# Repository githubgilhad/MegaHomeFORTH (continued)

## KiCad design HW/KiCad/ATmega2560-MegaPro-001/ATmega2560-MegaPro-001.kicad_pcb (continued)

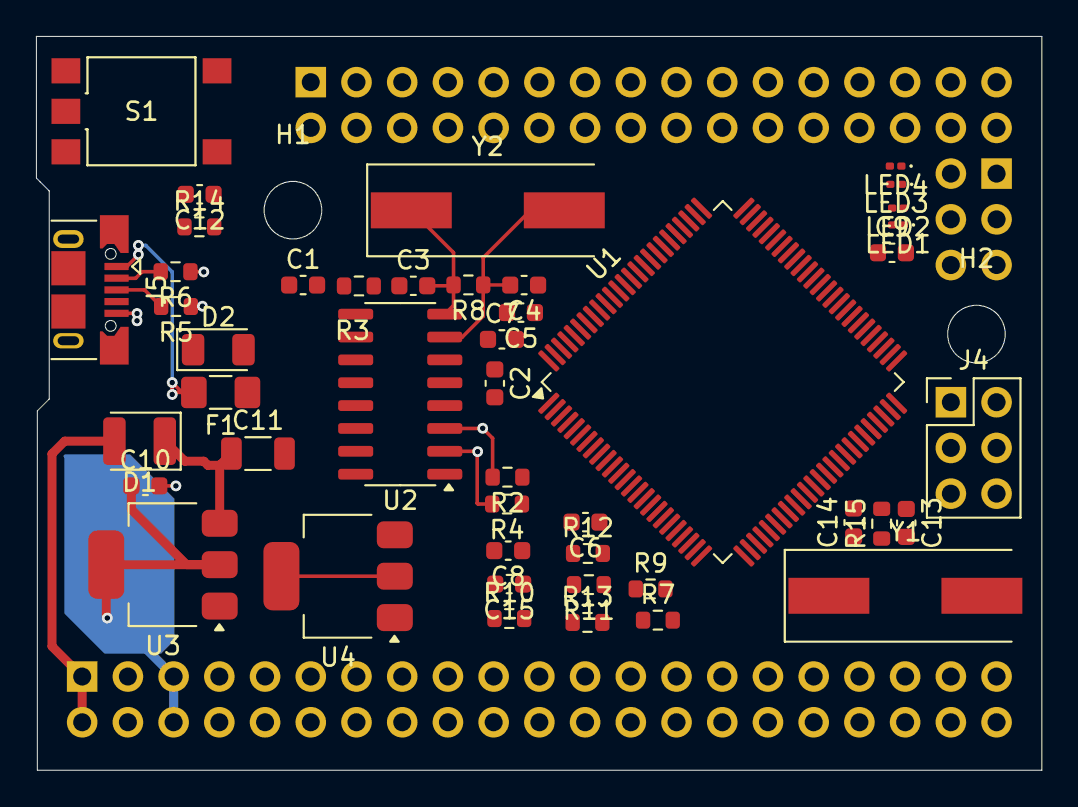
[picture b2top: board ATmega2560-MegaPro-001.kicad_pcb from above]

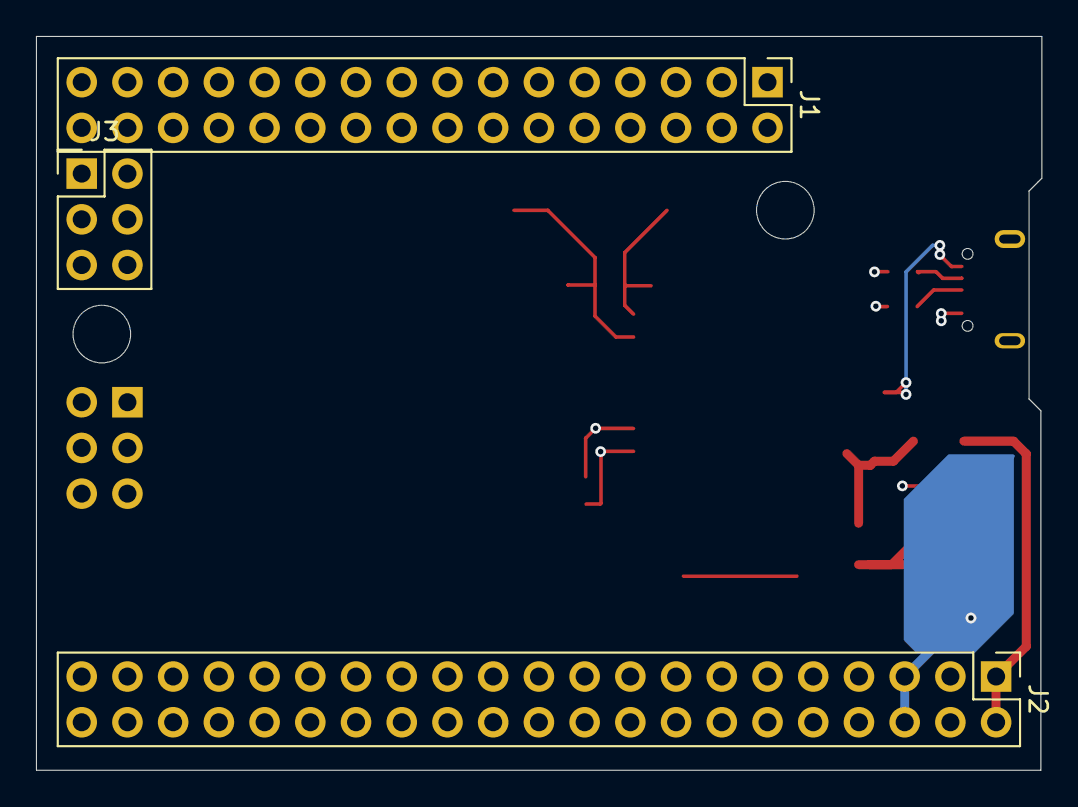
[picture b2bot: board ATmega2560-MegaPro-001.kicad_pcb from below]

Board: 2 copper layers, 55.9 x 40.8 mm, 50 parts (3 on the bottom side), 34 nets.

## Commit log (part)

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2025-06-14 uvodni commit
2025-06-14 Initial site population
2025-06-14 Idea pictures
2025-06-14 links
2025-06-15 PE7 problem
2025-06-15 FORTH testing
2025-06-15 better formating
2025-06-16 mapping pins
2025-06-17 check, what NanoHomeComputer SW uses, timers
2025-06-18 FORTH sources
2025-06-18 + 2025.06.18 Journal
2025-06-19 timers - pins table
2025-06-19 timers - pins table fixed
2025-06-19 Timers and pins table + some assignemnts
2025-06-19 +libs
2025-06-19 typo
2025-06-20 +tools for 24bit
2025-06-21 VGA works, picture, osciloscope, theory
2025-06-21 _nano.4th for pin assignment tests
2025-06-21 documentation
2025-06-25 Arduino Mega Pro - begin
2025-06-25 ATmega2560-MegaPro-001
2025-06-25 ATmega2560-MegaPro-001 schema
2025-06-27 +3d models, +Pins.rst, some reorganisation
2025-07-01 +Schema-8bitComp
2025-07-02 +docs/graphic_card.rst
2025-07-04 graphic_card - boot part OK, go for runtime
2025-07-04 graphic_card - shared ram
2025-07-04 8bitComp schema updated
2025-07-04 +Comp24 footprint
2025-07-04 maybe it can fit?
2025-07-04 - mounting holes
2025-07-05 some labels
2025-07-06 schema MHF-001 maybe OK
2025-07-06 saved lot of pins by removing unnecessery/redundant signals
2025-07-07 +NetJoint
2025-07-08 cleaning
2025-07-12 added some connectors
2025-07-12 Final placement of parts (I hope)
2025-07-13 WayWayWay and other final touches
2025-07-13 condensators
2025-07-13 XTALs, AVCC, AREF
2025-07-13 Autorouting
2025-07-14 Completed
2025-07-14 gerber files
2025-07-21 lo8, hi8, hlo8
2025-07-27 SD_card
2025-07-27 SD_card + MHF-001 doc
2025-07-27 fix paths
2025-07-27 breakout works
2025-07-28 Improvements
2025-08-01 so0me notes
2025-08-01 MHF-002
2025-08-01 photos and tests
2025-08-02 VGA screen stabilised
2025-08-02 Keyboard stabilised
2025-08-04 formatting
2025-08-07 fixed 40x25 VGA, found first HW problem (just ugly font)
2025-08-09 SD tests, sometime works with VGA, sometimes not - need to improve SW later
2025-08-09 more Errata
2025-08-10 slowcat
2025-08-14 external memory
2025-08-15 +Schema-8bitComp-BW.png
2025-08-30 note about external RAM
2025-08-30 added SPI + SD libraries from Arduino for hacking
2025-08-30 FAKE millis - SD seems to work
2025-08-31 ch341.patch
2025-08-31 SD_CAT
2025-09-05 WORDSP ; fix 4+ -> 4D+
2025-09-06 .D - prints DOUBLE; strankovani slov
2025-09-06 +SD_TYPE
2025-09-09 emtestmanual OK, emtestauto fail and reset - IMHO faulty HW
2025-09-09 new branch
2025-09-09 +Snake.4th game
2025-09-09 MHF-001 photo
2025-09-09 link to PCBway
2025-09-09 link to PCBway project
2025-09-10 +BOM, +MHF-001a.png
2025-09-12 footprints for HandSoldering, some schema modifications
2025-09-15 +footprints
2025-09-22 +cp2102 +SDCard
2025-09-23 more small fixes
2025-09-23 +Switch
2025-09-24 fixing small problems
2025-10-01 footprints (maybe complete)
2025-10-01 +Snake.4th game
    (cherry picked from commit ee48b846ca28632eee771566f5f776013240e820)
2025-10-02 RCA video somehow works, but eats PS/2, need more fixes
2025-10-02 RCA video somehow works, but eats PS/2, need more fixes
    (cherry picked from commit 65ca875b51632968f30175eec0eb6f11a6a396ee)
2025-10-04 included all planned improvements
2025-10-08 MHF-002 routing full PCB, need add texts
2025-10-09 PDF for Cu+Silkscreen+Courtyards
2025-10-10 improved SystemBus and 3xAND, NOT
2025-10-11 3xAND routed
2025-10-13 D-Latch testpoints
2025-10-15 reset + I2C LED
2025-10-17 Final version of HW MHF-002
2025-10-18 redesigned PS/2 and RCA to 40/80 char sources, need route
2025-10-18 renumbered RAMs
2025-10-18 more renumbering
2025-10-29 Silkscreen, views
2025-10-31 README MHF-002
2025-10-31 link from root
2025-10-31 Generated Gerber files (PCBway needs names In1 I2 instead of VCC and GND)
2025-10-31 small picture
2025-12-12 +pictures, VGA pin change
2025-12-28 New photos
2026-01-09 +photos/
2026-01-09 same_sequence.py
2026-01-09 more pictures
2026-03-08 add some files
2026-03-27 Snake in new FORTH works
2026-04-11 big snake photo
2026-04-15 DEMO SNAKE
2026-06-05 undefined_netclass = error
2026-06-23 +retro-002.png
